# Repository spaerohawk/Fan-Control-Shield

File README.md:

# Fan-Control-Shield
 ## Design files for Fan Control Shield for Nucleo f4x9zi.
  
 Designed by Chris Dougherty while a graduate student at Caltech. 
 
 These design files are open-sourced pursuant to requirements set forth by NASA's Jet Propulsion Laboratory (JPL). A total of two research-grade fan array wind tunnels (FAWTs) were designed and developed to assist experimental campaign efforts to chamber-test Ingenuity (Mars Helicopter) in simulated Martian forward flight conditions. Given the multi-sourcedness of fan arrays, printed circuit breakout boards that neatly interface with multiples of fan units designed to meet electrical/thermal specifications and off-gassing chamber requirements were set forth in the scope of work.
 
- A 11x11x1 fan array was constructed in the basement of GALCIT using the Fan Control Shield found in release [v1.0.0](https://github.com/spaerohawk/Fan-Control-Shield/releases/tag/v1.0.0). 
* A 21x21x2 fan array[^1] was constructed in the 25-ft Space Simulator at JPL using the Fan Control Shield found in release [v1.1.0](https://github.com/spaerohawk/Fan-Control-Shield/releases/tag/v1.1.0).
  * Direct PDF access to the above noted paper can be found [here](https://rdcu.be/dcesM). 

[^1]: Veismann, M., Dougherty, C., Rabinovitch, J. et al. Low-density multi-fan wind tunnel design and testing for the Ingenuity Mars Helicopter. Exp Fluids 62, 193 (2021). https://doi.org/10.1007/s00348-021-03278-5

 Creative Commons Attribution/Share-Alike, all text above must be included in any redistribution. See license.txt for additional information.

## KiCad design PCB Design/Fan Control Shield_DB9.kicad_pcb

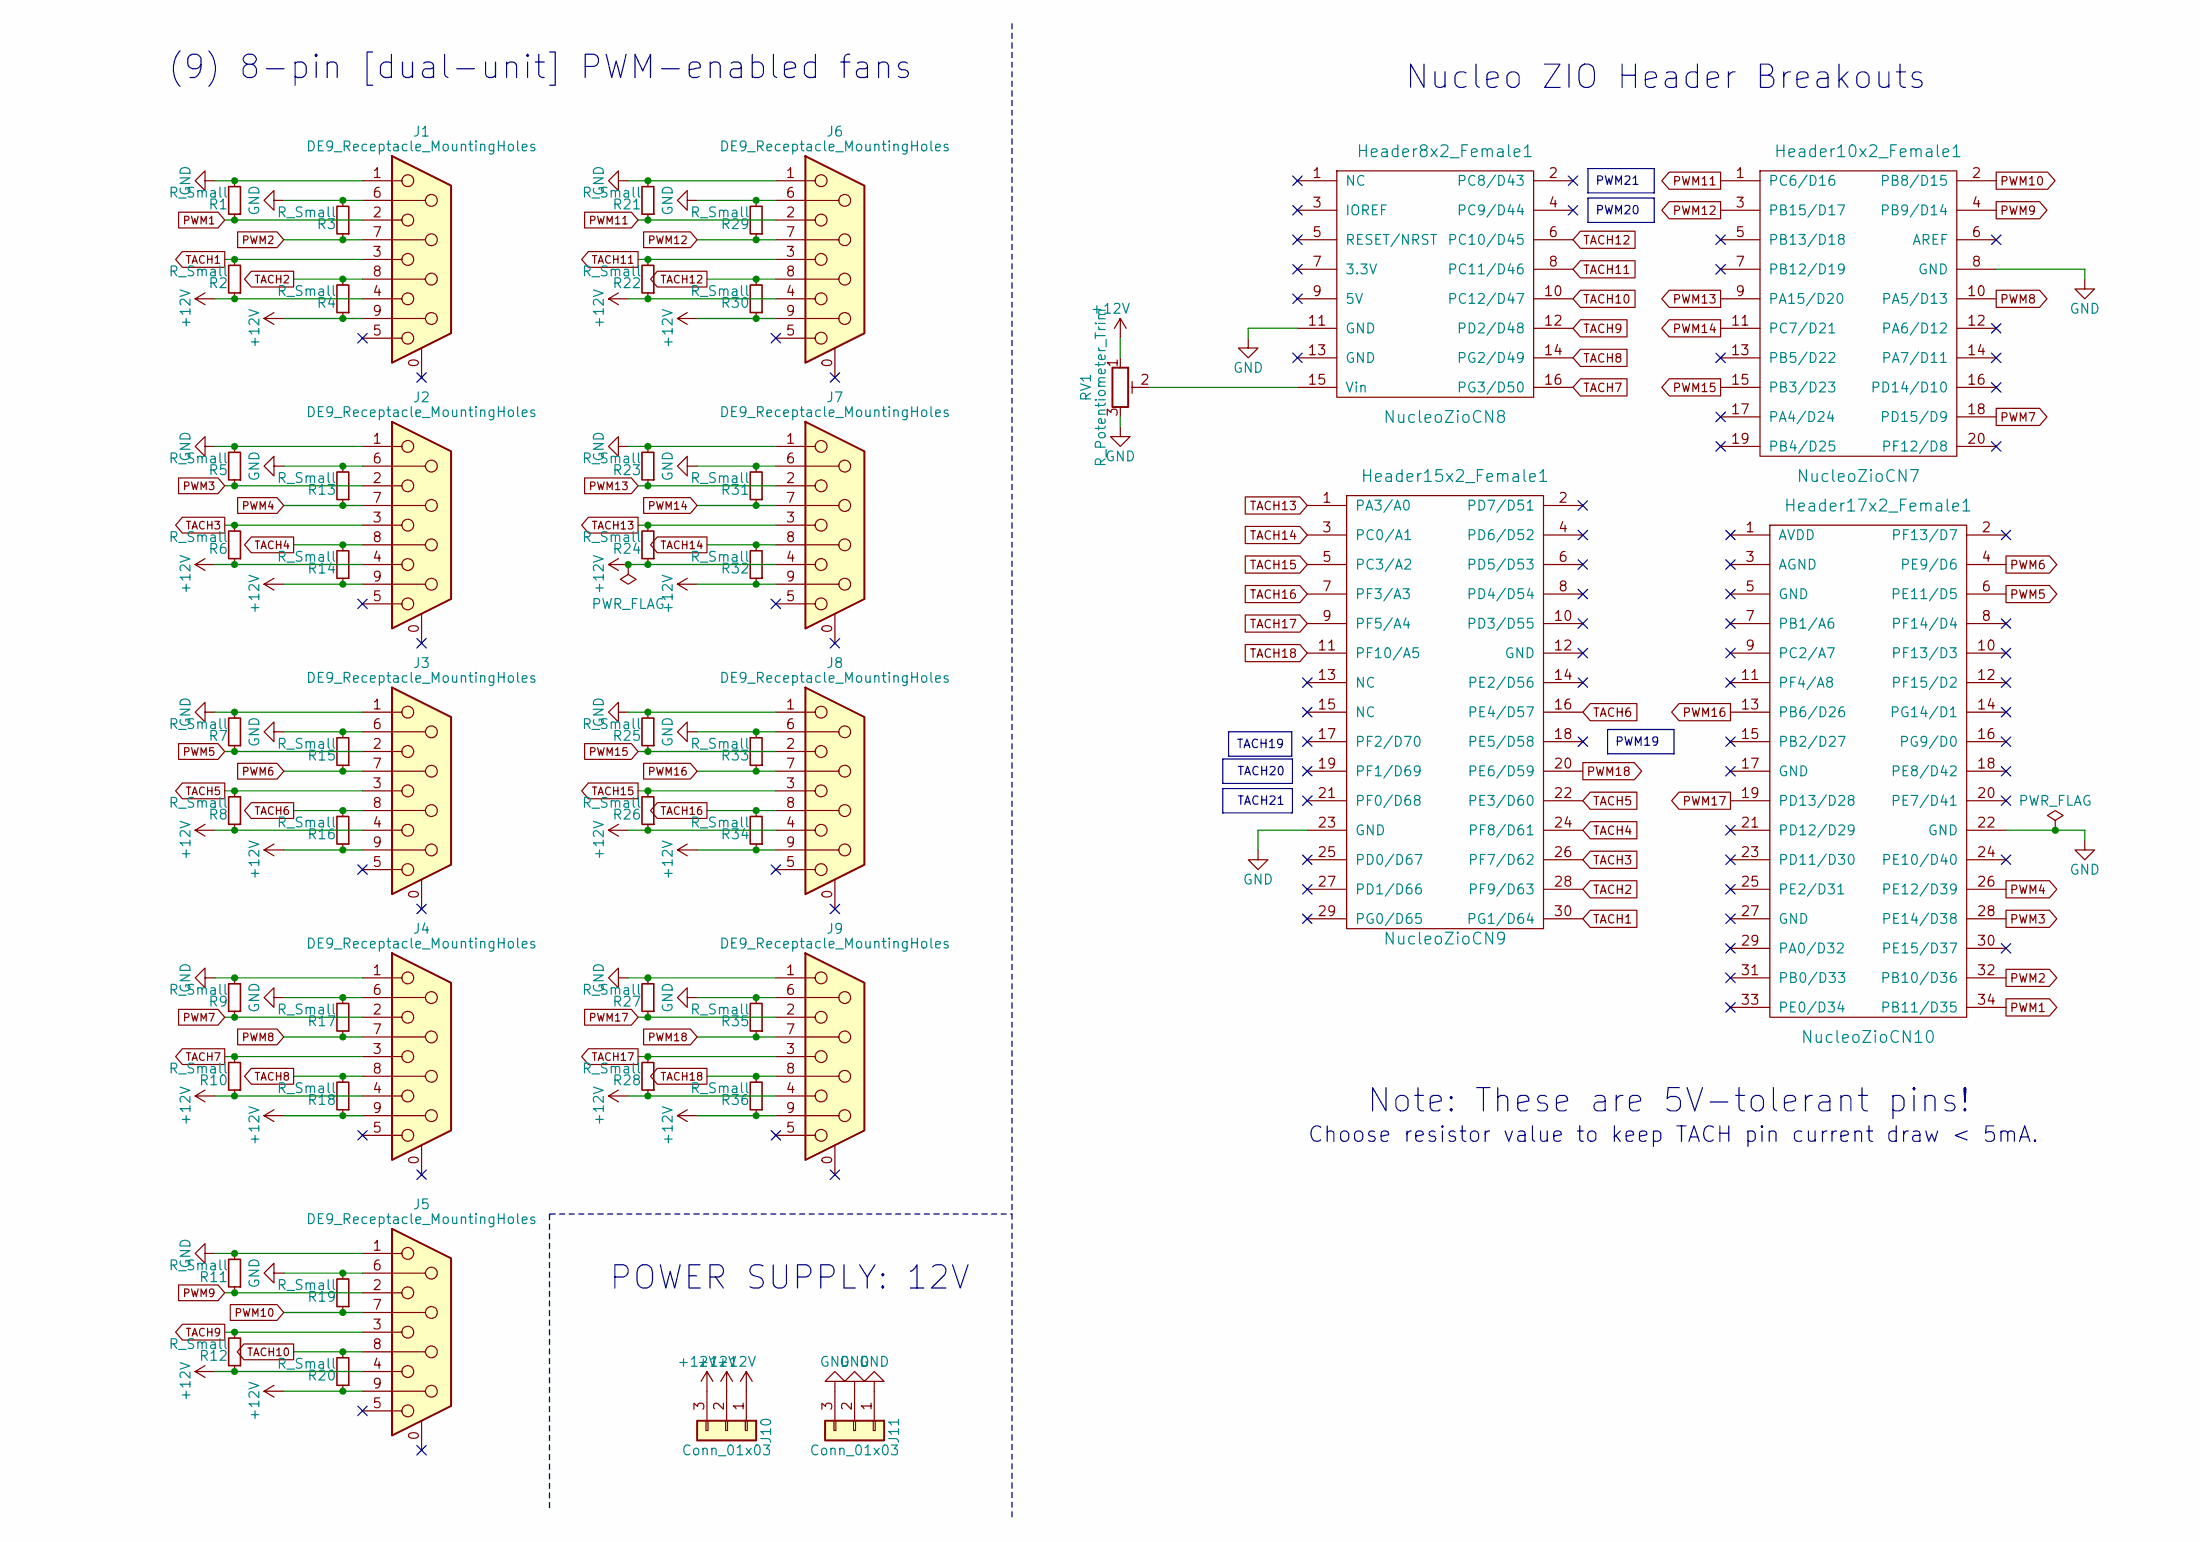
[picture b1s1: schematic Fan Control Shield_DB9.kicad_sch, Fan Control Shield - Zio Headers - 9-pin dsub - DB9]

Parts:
Header8x2_Female1: NucleoZioCN8; Socket_Strip_Straight_2x08_Pitch2.54mm
Header10x2_Female1: NucleoZioCN7; Socket_Strip_Straight_2x10_Pitch2.54mm
Header15x2_Female1: NucleoZioCN9; Socket_Strip_Straight_2x15_Pitch2.54mm
Header17x2_Female1: NucleoZioCN10; Socket_Strip_Straight_2x17_Pitch2.54mm
J1, J2, J3, J4, J5, J6, J7, J8, J9: DE9_Receptacle_MountingHoles; DSUB-9_Female_Vertical_P2.77x2.84mm_MountingHoles
J10, J11: Conn_01x03; CONN-TE-AMP3_P9.52
R1, R2, R3, R4, R5, R6, R7, R8, R9, R10, R11, R12, R13, R14, R15, R16, R17, R18, R19, R20, R21, R22, R23, R24, R25, R26, R27, R28, R29, R30, R31, R32, R33, R34, R35, R36: R_Small; R_1206_HandSoldering
RV1: R_Potentiometer_Trim; Potentiometer_Bourns_3266Y_Vertical

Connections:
+12V: J1.4, J1.9, J2.4, J2.9, J3.4, J3.9, J4.4, J4.9, J5.4, J5.9, J6.4, J6.9, J7.4, J7.9, J8.4, J8.9, J9.4, J9.9, J10.1, J10.2, J10.3, R2.1, R4.1, R6.1, R8.1, R10.1, R12.1, R14.1, R16.1, R18.1, R20.1, R22.1, R24.1, R26.1, R28.1, R30.1, R32.1, R34.1, R36.1, RV1.1
GND: Header8x2_Female1.11 (GND), Header10x2_Female1.8 (GND), Header15x2_Female1.23 (GND), Header17x2_Female1.22 (GND), J1.1, J1.6, J2.1, J2.6, J3.1, J3.6, J4.1, J4.6, J5.1, J5.6, J6.1, J6.6, J7.1, J7.6, J8.1, J8.6, J9.1, J9.6, J11.1, J11.2, J11.3, R1.2, R3.2, R5.2, R7.2, R9.2, R11.2, R13.2, R15.2, R17.2, R19.2, R21.2, R23.2, R25.2, R27.2, R29.2, R31.2, R33.2, R35.2, RV1.3; also elsewhere on the board
unnamed 2: Header8x2_Female1.15 (Vin), RV1.2; also elsewhere on the board
PWM1: Header17x2_Female1.34 (PB11/D35), J1.2, R1.1; also elsewhere on the board
PWM2: Header17x2_Female1.32 (PB10/D36), J1.7, R3.1; also elsewhere on the board
PWM3: Header17x2_Female1.28 (PE14/D38), J2.2, R5.1; also elsewhere on the board
PWM4: Header17x2_Female1.26 (PE12/D39), J2.7, R13.1; also elsewhere on the board
PWM5: Header17x2_Female1.6 (PE11/D5), J3.2, R7.1; also elsewhere on the board
PWM6: Header17x2_Female1.4 (PE9/D6), J3.7, R15.1; also elsewhere on the board
PWM7: Header10x2_Female1.18 (PD15/D9), J4.2, R9.1; also elsewhere on the board
PWM8: Header10x2_Female1.10 (PA5/D13), J4.7, R17.1; also elsewhere on the board
PWM9: Header10x2_Female1.4 (PB9/D14), J5.2, R11.1; also elsewhere on the board
PWM10: Header10x2_Female1.2 (PB8/D15), J5.7, R19.1; also elsewhere on the board
PWM11: Header10x2_Female1.1 (PC6/D16), J6.2, R21.1; also elsewhere on the board
PWM12: Header10x2_Female1.3 (PB15/D17), J6.7, R29.1; also elsewhere on the board
PWM13: Header10x2_Female1.9 (PA15/D20), J7.2, R23.1; also elsewhere on the board
PWM14: Header10x2_Female1.11 (PC7/D21), J7.7, R31.1; also elsewhere on the board
PWM15: Header10x2_Female1.15 (PB3/D23), J8.2, R25.1; also elsewhere on the board
PWM16: Header17x2_Female1.13 (PB6/D26), J8.7, R33.1; also elsewhere on the board
PWM17: Header17x2_Female1.19 (PD13/D28), J9.2, R27.1; also elsewhere on the board
PWM18: Header15x2_Female1.20 (PE6/D59), J9.7, R35.1; also elsewhere on the board
TACH1: Header15x2_Female1.30 (PG1/D64), J1.3, R2.2; also elsewhere on the board
TACH2: Header15x2_Female1.28 (PF9/D63), J1.8, R4.2; also elsewhere on the board
TACH3: Header15x2_Female1.26 (PF7/D62), J2.3, R6.2; also elsewhere on the board
TACH4: Header15x2_Female1.24 (PF8/D61), J2.8, R14.2; also elsewhere on the board
TACH5: Header15x2_Female1.22 (PE3/D60), J3.3, R8.2; also elsewhere on the board
TACH6: Header15x2_Female1.16 (PE4/D57), J3.8, R16.2; also elsewhere on the board
TACH7: Header8x2_Female1.16 (PG3/D50), J4.3, R10.2; also elsewhere on the board
TACH8: Header8x2_Female1.14 (PG2/D49), J4.8, R18.2; also elsewhere on the board
TACH9: Header8x2_Female1.12 (PD2/D48), J5.3, R12.2; also elsewhere on the board
TACH10: Header8x2_Female1.10 (PC12/D47), J5.8, R20.2; also elsewhere on the board
TACH11: Header8x2_Female1.8 (PC11/D46), J6.3, R22.2; also elsewhere on the board
TACH12: Header8x2_Female1.6 (PC10/D45), J6.8, R30.2; also elsewhere on the board
TACH13: Header15x2_Female1.1 (PA3/A0), J7.3, R24.2; also elsewhere on the board
TACH14: Header15x2_Female1.3 (PC0/A1), J7.8, R32.2; also elsewhere on the board
TACH15: Header15x2_Female1.5 (PC3/A2), J8.3, R26.2; also elsewhere on the board
TACH16: Header15x2_Female1.7 (PF3/A3), J8.8, R34.2; also elsewhere on the board
TACH17: Header15x2_Female1.9 (PF5/A4), J9.3, R28.2; also elsewhere on the board
TACH18: Header15x2_Female1.11 (PF10/A5), J9.8, R36.2; also elsewhere on the board

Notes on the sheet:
PWM20
PWM21
TACH19
PWM19
TACH21
TACH20
POWER SUPPLY: 12V
(9) 8-pin [dual-unit] PWM-enabled fans
Nucleo ZIO Header Breakouts
Choose resistor value to keep TACH pin current draw < 5mA.
Note: These are 5V-tolerant pins!

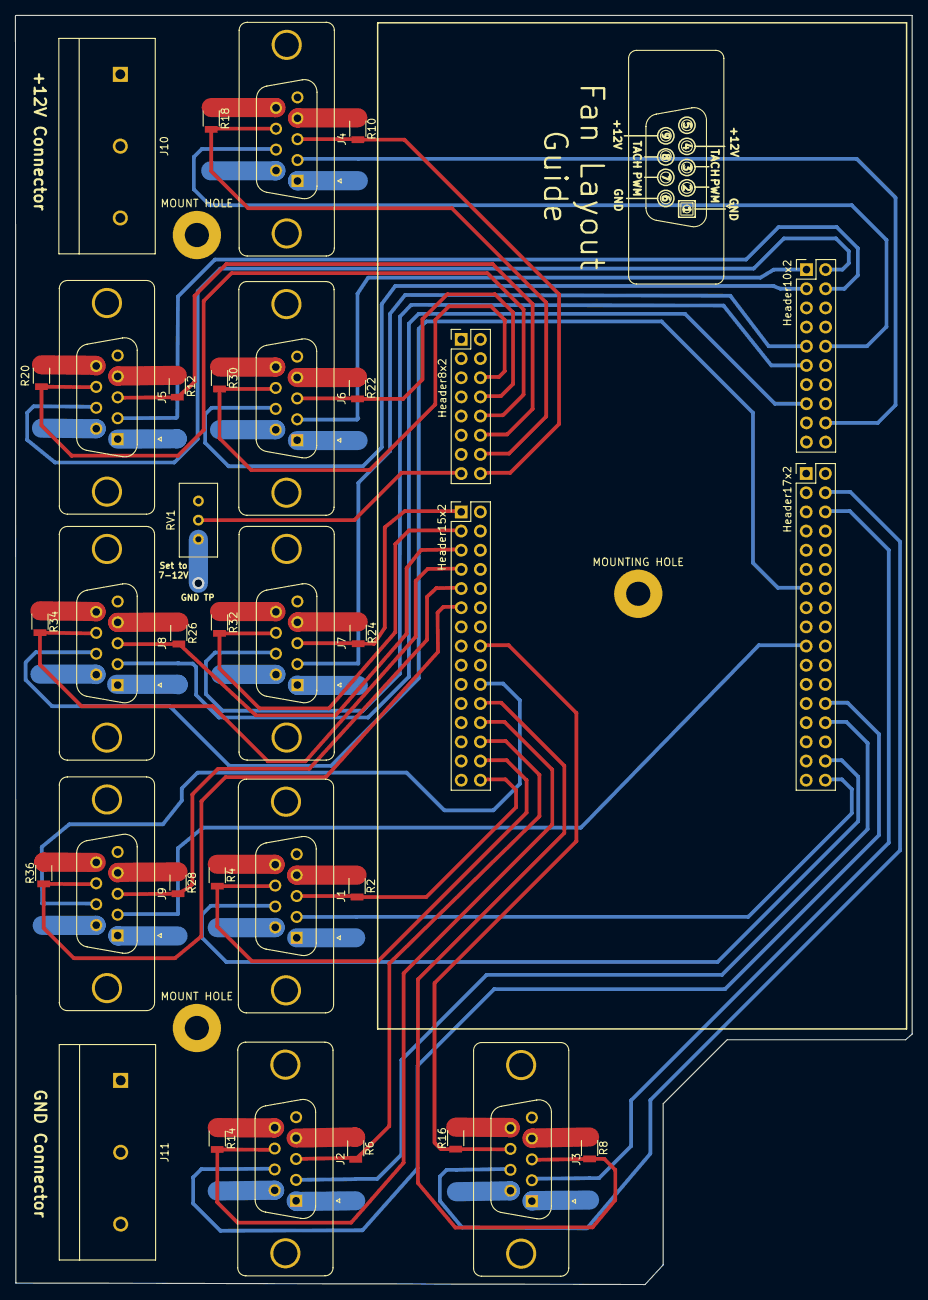
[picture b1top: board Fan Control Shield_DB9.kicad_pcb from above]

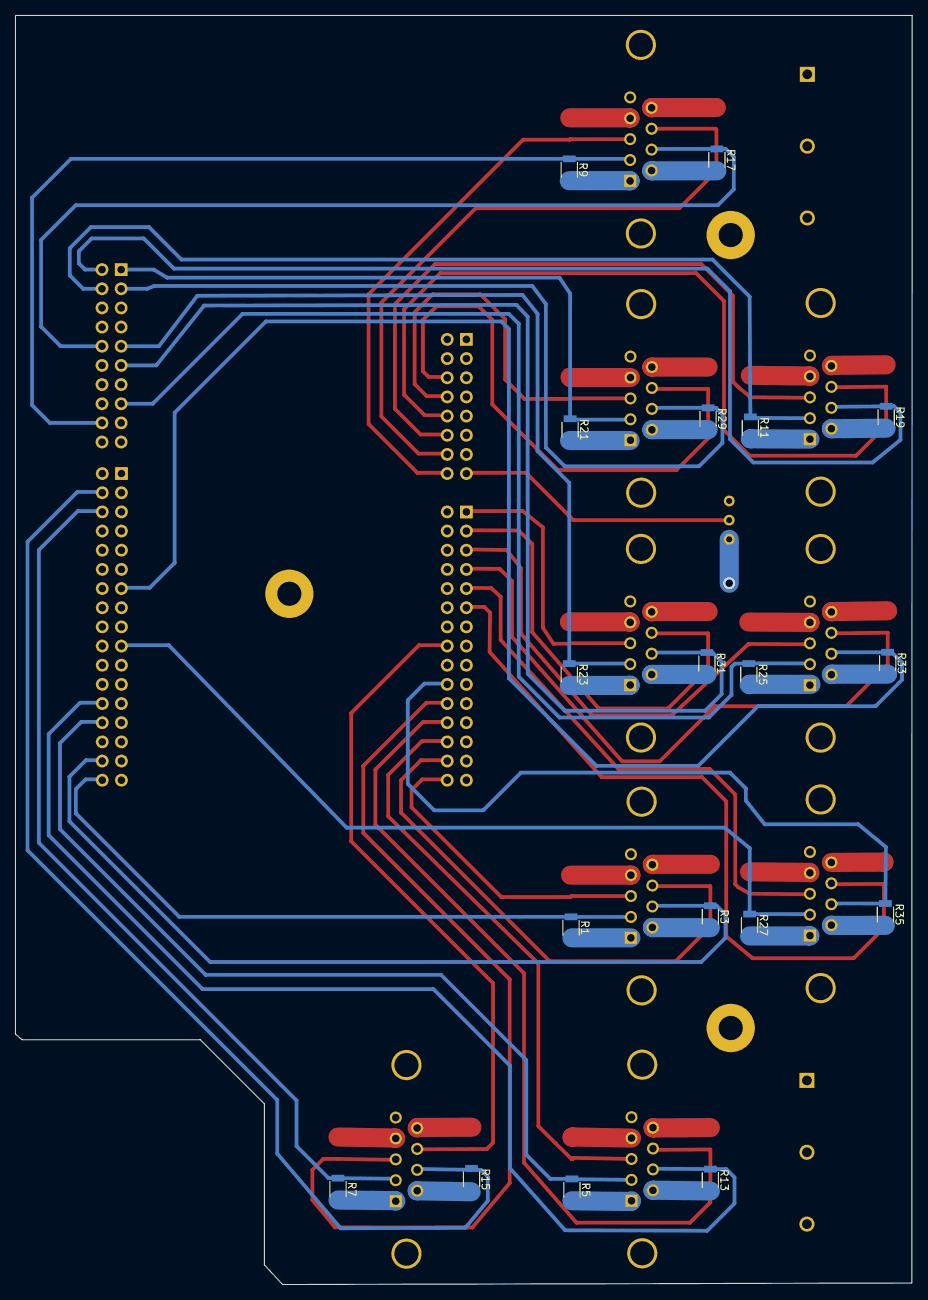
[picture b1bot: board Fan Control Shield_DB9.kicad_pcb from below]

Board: 4 copper layers, 118.8 x 168.2 mm, 56 parts (18 on the bottom side), 39 nets.

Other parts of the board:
Fan Layout Guide: Fan Layout Guide; Fan Layout Guide - DB9
Header8x2: NucleoZioCN8; Socket_Strip_Straight_2x08_Pitch2.54mm
Header10x2: NucleoZioCN7; Socket_Strip_Straight_2x10_Pitch2.54mm
Header15x2: NucleoZioCN9; Socket_Strip_Straight_2x15_Pitch2.54mm
Header17x2: NucleoZioCN10; Socket_Strip_Straight_2x17_Pitch2.54mm
MOUNT HOLE: MountingHole_3.2mm_M3_Pad
MOUNT HOLE#2: MountingHole_3.2mm_M3_Pad
MOUNTING HOLE: MountingHole_3.2mm_M3_Pad

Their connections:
GND: Header8x2.11 (GND), Header10x2.8 (GND), Header15x2.23 (GND), Header17x2.22 (GND); also elsewhere on the board
unnamed 2: Header8x2.15 (Vin); also elsewhere on the board
PWM1: Header17x2.34 (PB11/D35); also elsewhere on the board
PWM2: Header17x2.32 (PB10/D36); also elsewhere on the board
PWM3: Header17x2.28 (PE14/D38); also elsewhere on the board
PWM4: Header17x2.26 (PE12/D39); also elsewhere on the board
PWM5: Header17x2.6 (PE11/D5); also elsewhere on the board
PWM6: Header17x2.4 (PE9/D6); also elsewhere on the board
PWM7: Header10x2.18 (PD15/D9); also elsewhere on the board
PWM8: Header10x2.10 (PA5/D13); also elsewhere on the board
PWM9: Header10x2.4 (PB9/D14); also elsewhere on the board
PWM10: Header10x2.2 (PB8/D15); also elsewhere on the board
PWM11: Header10x2.1 (PC6/D16); also elsewhere on the board
PWM12: Header10x2.3 (PB15/D17); also elsewhere on the board
PWM13: Header10x2.9 (PA15/D20); also elsewhere on the board
PWM14: Header10x2.11 (PC7/D21); also elsewhere on the board
PWM15: Header10x2.15 (PB3/D23); also elsewhere on the board
PWM16: Header17x2.13 (PB6/D26); also elsewhere on the board
PWM17: Header17x2.19 (PD13/D28); also elsewhere on the board
PWM18: Header15x2.20 (PE6/D59); also elsewhere on the board
TACH1: Header15x2.30 (PG1/D64); also elsewhere on the board
TACH2: Header15x2.28 (PF9/D63); also elsewhere on the board
TACH3: Header15x2.26 (PF7/D62); also elsewhere on the board
TACH4: Header15x2.24 (PF8/D61); also elsewhere on the board
TACH5: Header15x2.22 (PE3/D60); also elsewhere on the board
TACH6: Header15x2.16 (PE4/D57); also elsewhere on the board
TACH7: Header8x2.16 (PG3/D50); also elsewhere on the board
TACH8: Header8x2.14 (PG2/D49); also elsewhere on the board
TACH9: Header8x2.12 (PD2/D48); also elsewhere on the board
TACH10: Header8x2.10 (PC12/D47); also elsewhere on the board
TACH11: Header8x2.8 (PC11/D46); also elsewhere on the board
TACH12: Header8x2.6 (PC10/D45); also elsewhere on the board
TACH13: Header15x2.1 (PA3/A0); also elsewhere on the board
TACH14: Header15x2.3 (PC0/A1); also elsewhere on the board
TACH15: Header15x2.5 (PC3/A2); also elsewhere on the board
TACH16: Header15x2.7 (PF3/A3); also elsewhere on the board
TACH17: Header15x2.9 (PF5/A4); also elsewhere on the board
TACH18: Header15x2.11 (PF10/A5); also elsewhere on the board

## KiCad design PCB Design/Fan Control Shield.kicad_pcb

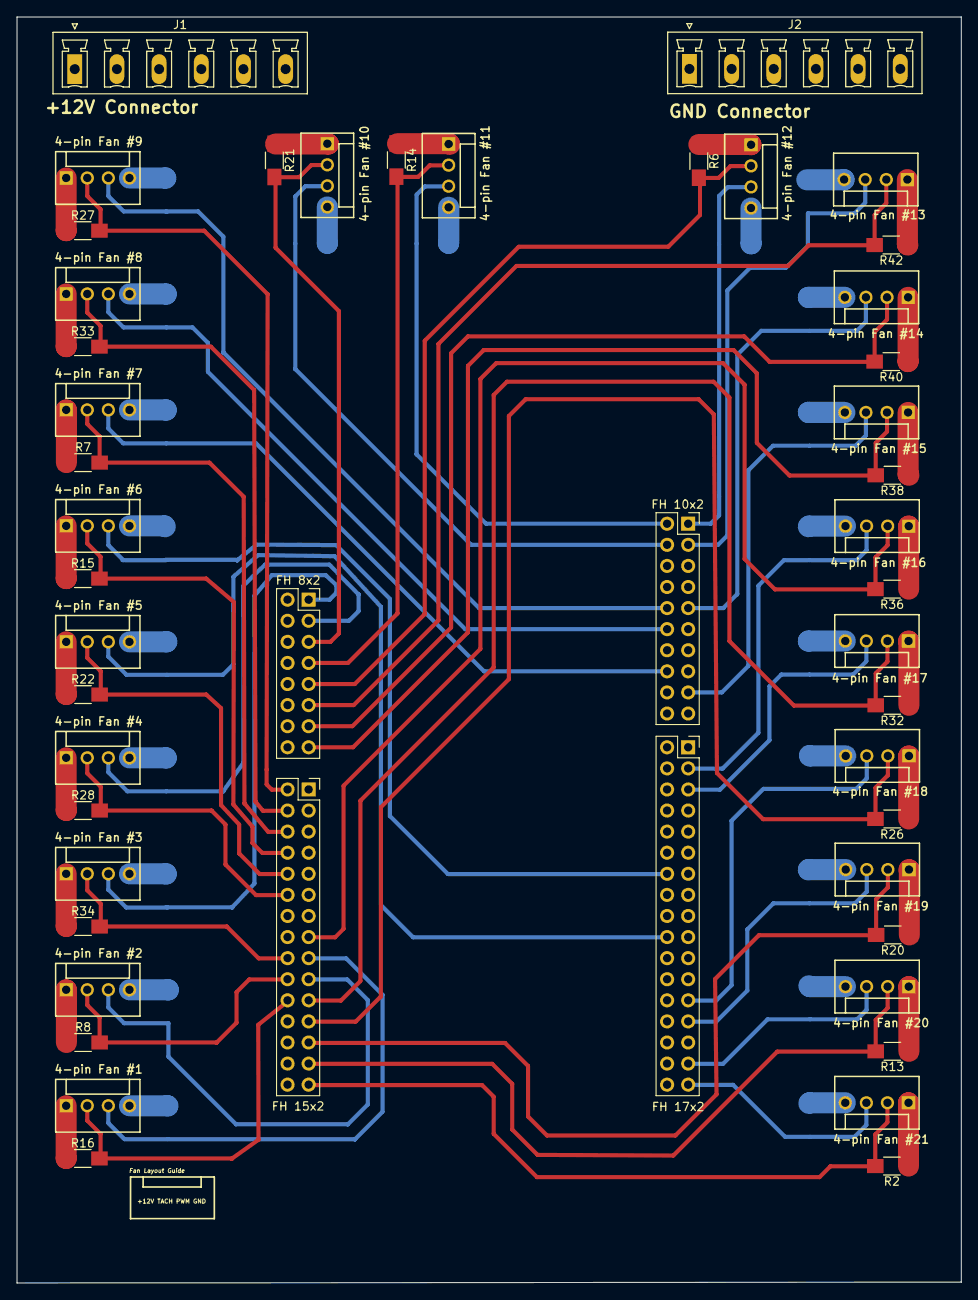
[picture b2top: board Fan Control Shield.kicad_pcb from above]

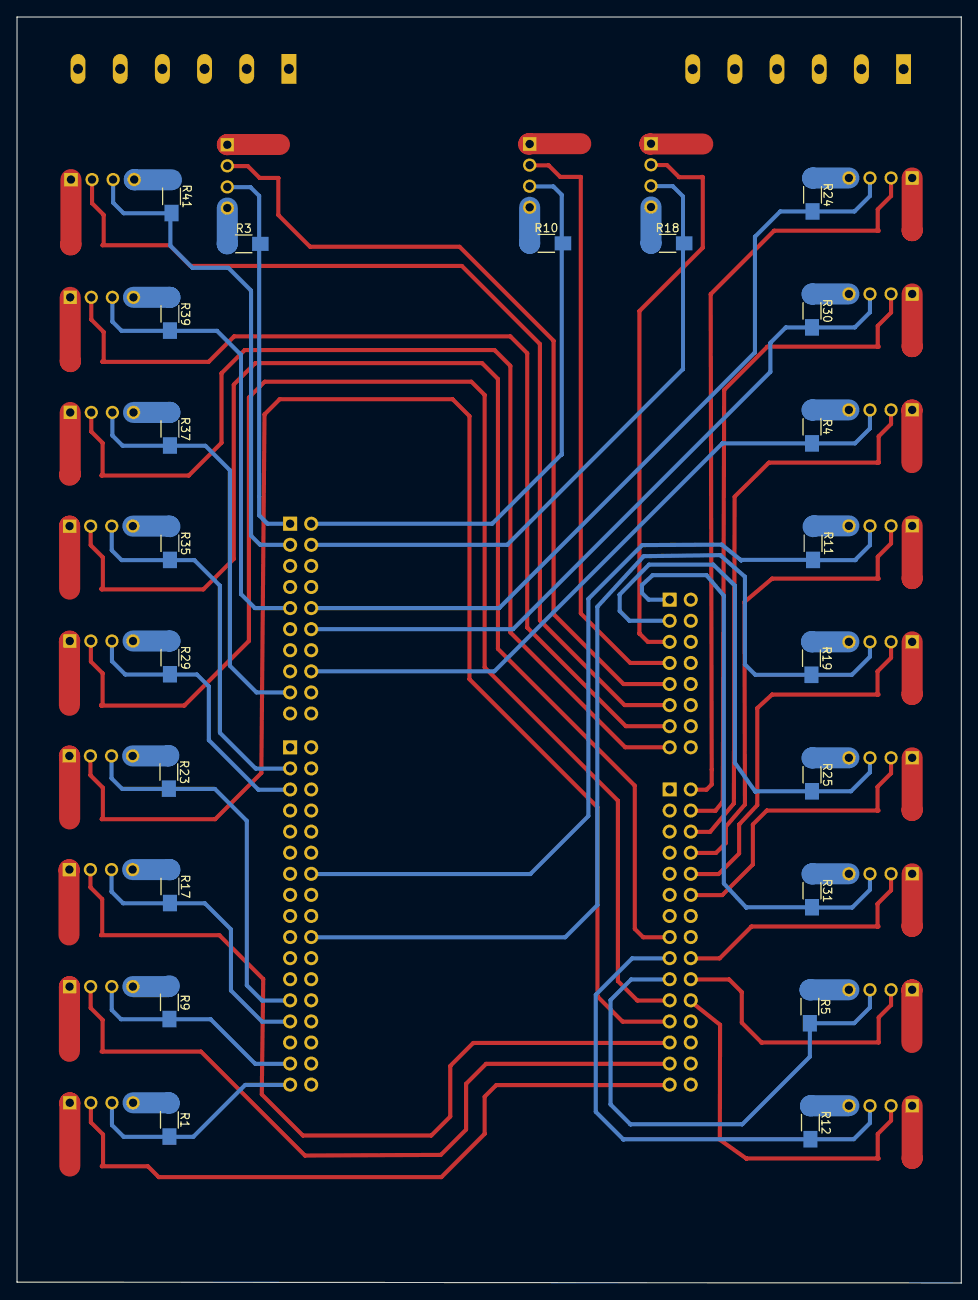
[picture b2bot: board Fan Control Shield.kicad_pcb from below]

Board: 4 copper layers, 113.8 x 152.5 mm, 69 parts (21 on the bottom side), 44 nets.

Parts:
4-pin Fan #1, 4-pin Fan #2, 4-pin Fan #3, 4-pin Fan #4, 4-pin Fan #5, 4-pin Fan #6, 4-pin Fan #7, 4-pin Fan #8, 4-pin Fan #9 , 4-pin Fan #10, 4-pin Fan #11, 4-pin Fan #12, 4-pin Fan #13, 4-pin Fan #14, 4-pin Fan #15, 4-pin Fan #16, 4-pin Fan #17, 4-pin Fan #18, 4-pin Fan #19, 4-pin Fan #20, 4-pin Fan #21: Fan_Connector; MOLEX-22-23-2041_nucleo
FH 8x2: NucleoZioCN8; Socket_Strip_Straight_2x08_Pitch2.54mm
FH 10x2: NucleoZioCN7; Socket_Strip_Straight_2x10_Pitch2.54mm
FH 15x2: NucleoZioCN9; Socket_Strip_Straight_2x15_Pitch2.54mm
FH 17x2: NucleoZioCN10; Socket_Strip_Straight_2x17_Pitch2.54mm
J1, J2: CONN_01X06; PhoenixContact_MCV-G_06x5.08mm_Vertical
R1, R2, R3, R4, R5, R6, R7, R8, R9, R10, R11, R12, R13, R14, R15, R16, R17, R18, R19, R20, R21, R22, R23, R24, R25, R26, R27, R28, R29, R30, R31, R32, R33, R34, R35, R36, R37, R38, R39, R40, R41, R42: 4.7K; R_1206_HandSoldering

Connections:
+12V: 4-pin Fan #1.4, 4-pin Fan #2.4, 4-pin Fan #3.4, 4-pin Fan #4.4, 4-pin Fan #5.4, 4-pin Fan #6.4, 4-pin Fan #7.4, 4-pin Fan #8.4, 4-pin Fan #9.4, 4-pin Fan #10.4, 4-pin Fan #11.4, 4-pin Fan #12.4, 4-pin Fan #13.4, 4-pin Fan #14.4, 4-pin Fan #15.4, 4-pin Fan #16.4, 4-pin Fan #17.4, 4-pin Fan #18.4, 4-pin Fan #19.4, 4-pin Fan #20.4, 4-pin Fan #21.4, J1.1, J1.2, J1.3, J1.4, J1.5, J1.6, R2.1, R6.1, R7.1, R8.1, R13.1, R14.1, R15.1, R16.1, R20.1, R21.1, R22.1, R26.1, R27.1, R28.1, R32.1, R33.1, R34.1, R36.1, R38.1, R40.1, R42.1
GND: 4-pin Fan #1.1, 4-pin Fan #2.1, 4-pin Fan #3.1, 4-pin Fan #4.1, 4-pin Fan #5.1, 4-pin Fan #6.1, 4-pin Fan #7.1, 4-pin Fan #8.1, 4-pin Fan #9.1, 4-pin Fan #10.1, 4-pin Fan #11.1, 4-pin Fan #12.1, 4-pin Fan #13.1, 4-pin Fan #14.1, 4-pin Fan #15.1, 4-pin Fan #16.1, 4-pin Fan #17.1, 4-pin Fan #18.1, 4-pin Fan #19.1, 4-pin Fan #20.1, 4-pin Fan #21.1, FH 8x2.11, FH 10x2.8, FH 15x2.23, FH 17x2.22, J2.1, J2.2, J2.3, J2.4, J2.5, J2.6, R1.1, R3.1, R4.1, R5.1, R9.1, R10.1, R11.1, R12.1, R17.1, R18.1, R19.1, R23.1, R24.1, R25.1, R29.1, R30.1, R31.1, R35.1, R37.1, R39.1, R41.1
PWM1: 4-pin Fan #21.2, FH 17x2.34, R1.2
PWM2: 4-pin Fan #20.2, FH 17x2.32, R9.2
PWM3: 4-pin Fan #19.2, FH 17x2.28, R17.2
PWM4: 4-pin Fan #18.2, FH 17x2.26, R23.2
PWM5: 4-pin Fan #17.2, FH 17x2.6, R29.2
PWM6: 4-pin Fan #16.2, FH 17x2.4, R35.2
PWM7: 4-pin Fan #15.2, FH 10x2.18, R37.2
PWM8: 4-pin Fan #14.2, FH 10x2.10, R39.2
PWM9: 4-pin Fan #13.2, FH 10x2.4, R41.2
PWM10: 4-pin Fan #12.2, FH 10x2.2, R3.2
PWM11: 4-pin Fan #11.2, FH 10x2.1, R10.2
PWM12: 4-pin Fan #10.2, FH 10x2.3, R18.2
PWM13: 4-pin Fan #9.2, FH 10x2.9, R24.2
PWM14: 4-pin Fan #8.2, FH 10x2.11, R30.2
PWM15: 4-pin Fan #7.2, FH 10x2.15, R4.2
PWM16: 4-pin Fan #6.2, FH 17x2.13, R11.2
PWM17: 4-pin Fan #5.2, FH 17x2.19, R19.2
PWM18: 4-pin Fan #2.2, FH 15x2.20, R5.2
PWM19: 4-pin Fan #1.2, FH 15x2.18, R12.2
PWM20: 4-pin Fan #4.2, FH 8x2.4, R25.2
PWM21: 4-pin Fan #3.2, FH 8x2.2, R31.2
TACH1: 4-pin Fan #21.3, FH 15x2.30, R2.2
TACH2: 4-pin Fan #20.3, FH 15x2.28, R13.2
TACH3: 4-pin Fan #19.3, FH 15x2.26, R20.2
TACH4: 4-pin Fan #18.3, FH 15x2.24, R26.2
TACH5: 4-pin Fan #17.3, FH 15x2.22, R32.2
TACH6: 4-pin Fan #16.3, FH 15x2.16, R36.2
TACH7: 4-pin Fan #15.3, FH 8x2.16, R38.2
TACH8: 4-pin Fan #14.3, FH 8x2.14, R40.2
TACH9: 4-pin Fan #13.3, FH 8x2.12, R42.2
TACH10: 4-pin Fan #12.3, FH 8x2.10, R6.2
TACH11: 4-pin Fan #11.3, FH 8x2.8, R14.2
TACH12: 4-pin Fan #10.3, FH 8x2.6, R21.2
TACH13: 4-pin Fan #9.3, FH 15x2.1, R27.2
TACH14: 4-pin Fan #8.3, FH 15x2.3, R33.2
TACH15: 4-pin Fan #7.3, FH 15x2.5, R7.2
TACH16: 4-pin Fan #6.3, FH 15x2.7, R15.2
TACH17: 4-pin Fan #5.3, FH 15x2.9, R22.2
TACH18: 4-pin Fan #4.3, FH 15x2.11, R28.2
TACH19: 4-pin Fan #3.3, FH 15x2.17, R34.2
TACH20: 4-pin Fan #2.3, FH 15x2.19, R8.2
TACH21: 4-pin Fan #1.3, FH 15x2.21, R16.2

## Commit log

2023-05-15 Update .gitignore
    Include fp-lib-table.
    When project specific libraries are added in KiCAD, a fp-lib-table is generated locally.
    Will instead consider Library management with submodules.
2023-05-15 Add original design files (ported)
    Upload KiCAD source files originally created in 4.0.6 ported into 7.0.2.
    Automatic library footprint associations likely means (significant) design rule check errors.
    KiCAD moved to entirely different file naming convention and attempts to reconcile legacy files by re-saving in new format, but custom libraries do not seem to port over correctly, if at all.
2023-05-18 Delete original design files - kk254
    Moving away from antiquated original prototype (plastic 4-pin connectors do not meet current/thermal demands).
2023-05-18 Add new 9-pin dsub design files (ported)
    The fan control shield quickly evolved away from the original (21) 4-pin fan prototype shield in favor of the more robust, metallic, 5+ amp per pin current carrying capacity 9-pin dsub connectors, ab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
2023-05-18 Add support files
    Added a Documentation folder as well as submodule linking to Library repository
